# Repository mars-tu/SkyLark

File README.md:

# SkyLark
Repository of Drone named SkyLark by MARS capable of autonomous navigation for transfer of goods.

## Key Feature:-
* Autonomous robot with payload to carry for multiple purposes which is capable to move on RC control.
* Manipulate flight by gesture recognition.
* Runs on PX4 AutoPilot framework via ROS.

## Electro-mechanical design:

* Drone frame.

## Flight Controller Schematic:

## ROS Packages:
* [SkyLark package](#flying_skylark)

### flying_skylark
------------------
* This package contains all the files related to robot and its configuration 

### Setup and launching the simulation environment:-

* Clone the repo, build in your preferred system and add the following lines in your bashrc.
```
source ~/{name_of_workspace}/devel/setup.bash

source ~/{name_of_workspace}/src/PX4-Autopilot/Tools/setup_gazebo.bash ~/{name_of_workspace}/src/PX4-Autopilot/ ~/{name_of_workspace}/src/PX4-Autopilot/build/px4_sitl_default >> /dev/null

export ROS_PACKAGE_PATH=$ROS_PACKAGE_PATH:~/{name_of_workspace}/src/PX4-Autopilot

export ROS_PACKAGE_PATH=$ROS_PACKAGE_PATH:~/{name_of_workspace}/src/PX4-Autopilot/Tools/sitl_gazebo

```
* For making gazebo work with PX-4 autopilot 
```
cd ~/{name_of_workspace}/src/PX4-Autopilot/
make px4_sitl_default gazebo
```

* Command `roslaunch flying_skylark flying_square.launch` will launch the gazebo world along with the PX-4 autopilot.

### Simulation Video
Click on Image to play

## Prerequisites
* C++14
* python 2.x
* PX4 AutoPilot
* ROS Noetic
* Embedded C
* Raspberry pi 3B (setup given below)
* Eagle
* PTC Creo
#### Note: Hardware prerequisites mentioned in xyz section.

## Setup
* [Raspi + OS setup](#setting-up-cpu)

### Setting Up CPU
------------------
#### Installing Ubuntu and ROS on Raspberry pi
1) [Download](https://cdimage.ubuntu.com/releases/18.04/release/) the Ubuntu image for raspberry pi 3.
2) Flash the image with preferable software.
3) Follow the standard ARM installation instructions from [ROS Wiki](https://wiki.ros.org/melodic/Installation/Ubuntu) to install ROS Melodic.

#### Installing basic tools and setting them up
```
sudo apt-get update
sudo apt-get upgrade
sudo apt autoremove
```

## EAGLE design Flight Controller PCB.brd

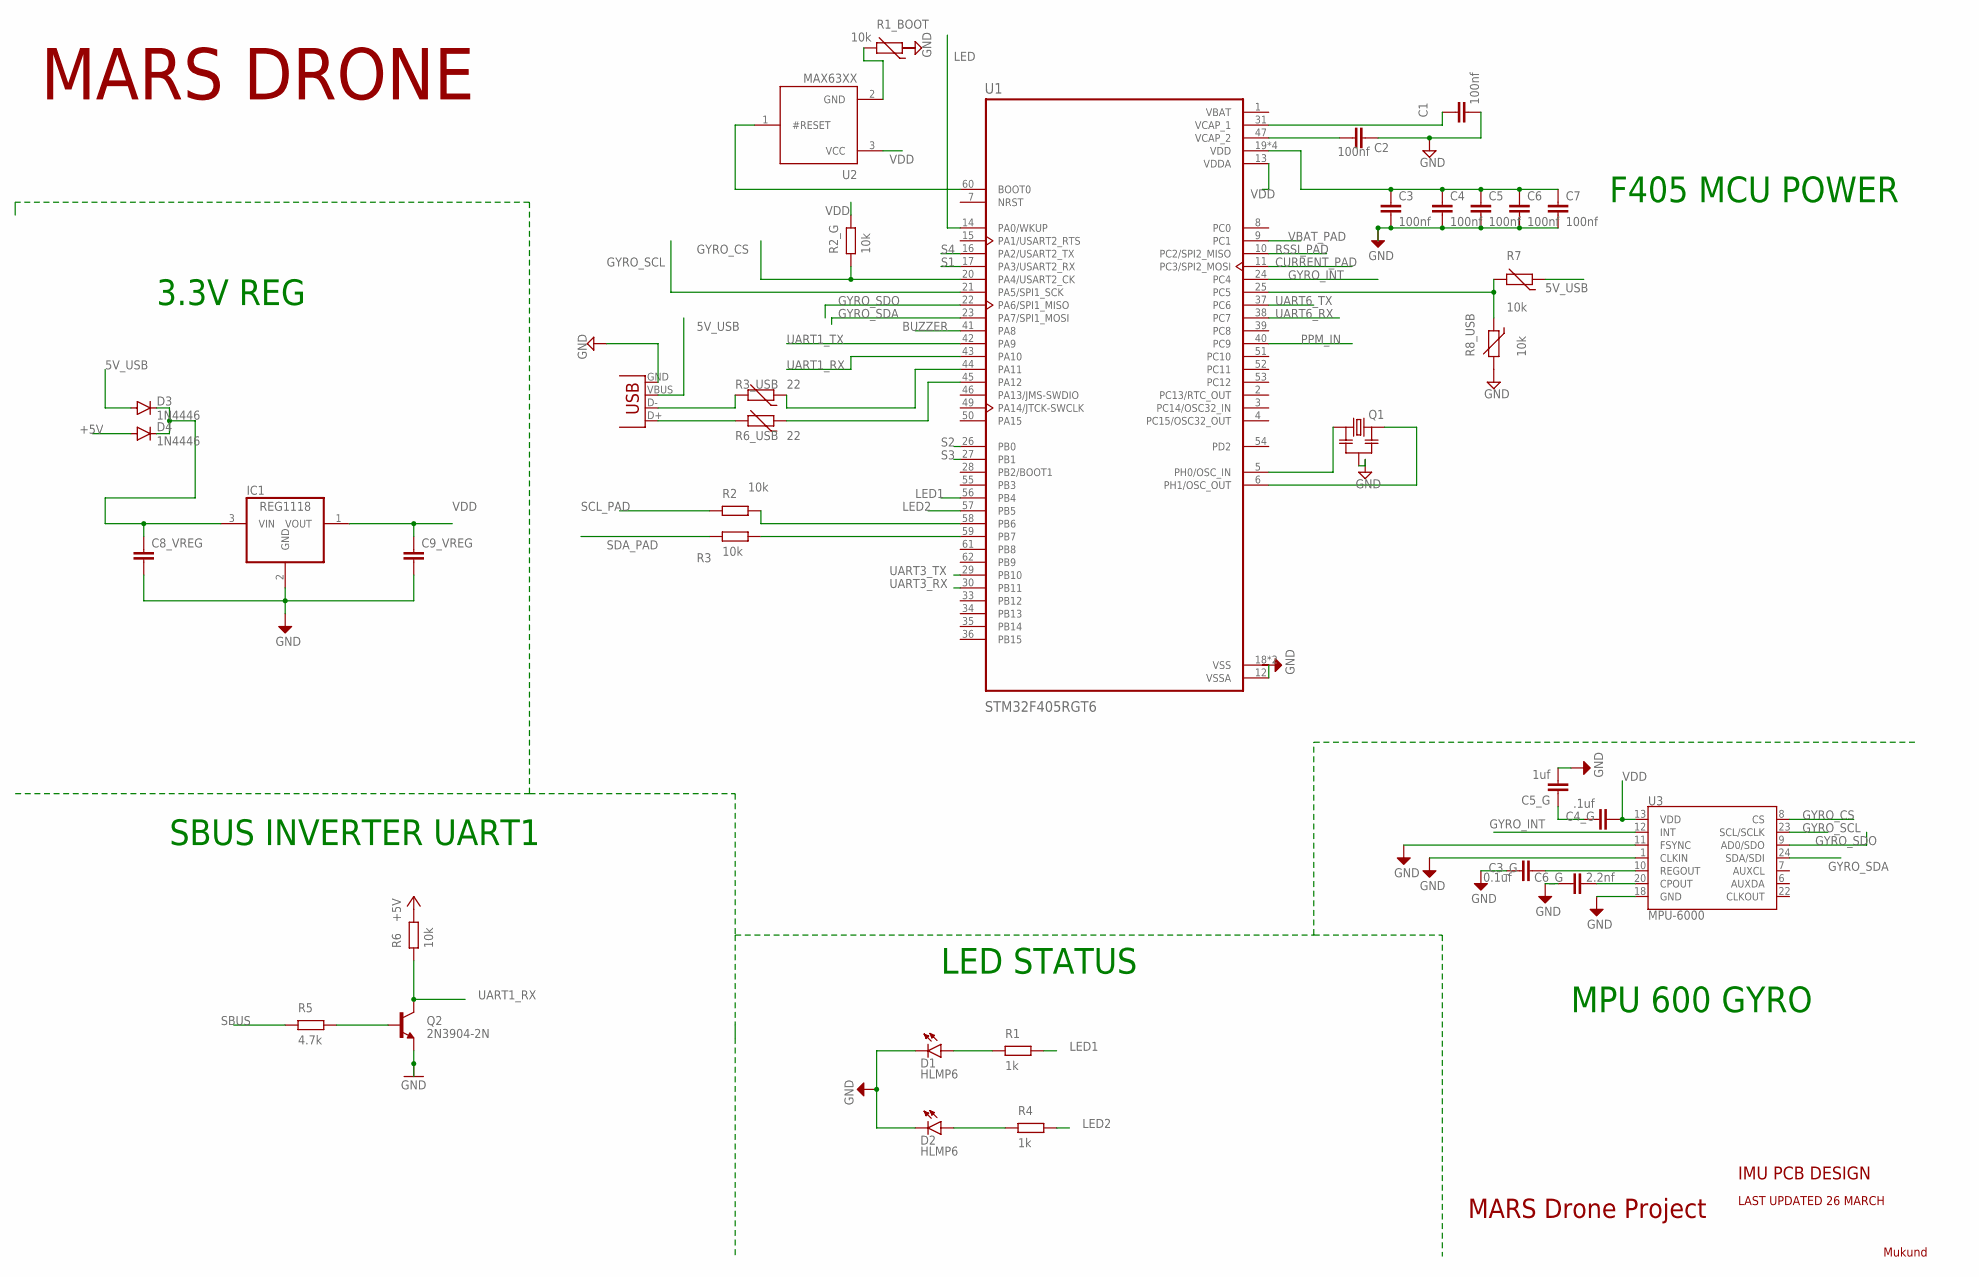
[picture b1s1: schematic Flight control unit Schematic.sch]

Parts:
C1, C2: 100nf; C2.5-3
C3, C4, C5, C6, C7: 100nf; C2.5-2
C3_G: 0.1uf; C2.5-3
C4_G: .1uf; C2.5-3
C5_G: 1uf; C2.5-3
C6_G: 2.2nf; C2.5-3
C8_VREG, C9_VREG: C2,5-3; C2.5-3
D1, D2: HLMP6
D3, D4: 1N4446; DO35-10
IC1: REG1118; SOT223
Q1: RESONATOR-MURATACST_CE; RESONATOR_MURATA2
Q2: 2N3904-2N; TO92
R1_BOOT, R7, R8_USB: 10k; RS-2,5
R3_USB, R6_USB: 22; RS-2,5
U1: STM32F405RGT6; QFP50P1200X1200X160-64N
U2: MAX63XX; SOT23
U3: MPU-6000; QFN-24-EP
X1: USB-A-S

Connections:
5V_USB: D3.A, R7.1, X1.VBUS
+5V: D4.A
BUZZER: U1.41 (PA8)
CURRENT_PAD: U1.11 (PC3/SPI2_MOSI)
GND: C1.2, C2.2, C3.2, C3_G.1, C4.2, C5.2, C5_G.2, C6.2, C6_G.1, C7.2, C8_VREG.2, C9_VREG.2, D1.K, D2.K, IC1.2 (GND), Q1.2, Q2.3 (E), R8_USB.2, U3.1 (CLKIN), U3.11 (FSYNC), U3.18 (GND), X1.GND
GYRO_CS: U1.20 (PA4/USART2_CK), U3.8 (CS)
GYRO_INT: U1.24 (PC4), U3.12 (INT)
GYRO_SCL: U1.21 (PA5/SPI1_SCK), U3.23 (SCL/SCLK)
GYRO_SDA: U1.23 (PA7/SPI1_MOSI), U3.24 (SDA/SDI)
GYRO_SDO: U1.22 (PA6/SPI1_MISO), U3.9 (AD0/SDO)
LED: U1.14 (PA0/WKUP)
LED1: U1.56 (PB4)
LED2: U1.57 (PB5)
unnamed: C6_G.2, U3.20 (CPOUT)
unnamed: U1.12 (VSSA), U1.18 (VSS), U1.63 (VSS)
unnamed: C4_G.1, C5_G.1
unnamed: C3.1, C4.1, C5.1, C6.1, C7.1, U1.19 (VDD), U1.32 (VDD), U1.48 (VDD), U1.64 (VDD)
unnamed: C3_G.2, U3.10 (REGOUT)
unnamed: R3_USB.1, U1.44 (PA11)
unnamed: R6_USB.1, U1.45 (PA12)
unnamed: C8_VREG.1, D3.C, D4.C, IC1.3 (VIN)
unnamed: R7.2, R8_USB.1, U1.25 (PC5)
unnamed: C1.1, U1.31 (VCAP_1)
unnamed: C2.1, U1.47 (VCAP_2)
unnamed: U1.60 (BOOT0), U2.1 (#RESET)
unnamed: R1_BOOT.2, U2.2 (GND)
unnamed: R6_USB.2, X1.D+
unnamed: R3_USB.2, X1.D-
unnamed: Q1.1, U1.5 (PH0/OSC_IN)
unnamed: Q1.3, U1.6 (PH1/OSC_OUT)
PPM_IN: U1.40 (PC9)
RSSI_PAD: U1.10 (PC2/SPI2_MISO)
S1: U1.17 (PA3/USART2_RX)
S2: U1.26 (PB0)
S3: U1.27 (PB1)
S4: U1.16 (PA2/USART2_TX)
UART1_RX: Q2.1 (C), U1.43 (PA10)
UART1_TX: U1.42 (PA9)
UART3_RX: U1.30 (PB11)
UART3_TX: U1.29 (PB10)
UART6_RX: U1.38 (PC7)
UART6_TX: U1.37 (PC6)
VBAT: U1.1 (VBAT)
VBAT_PAD: U1.9 (PC1)
VDD: C4_G.2, C9_VREG.1, IC1.1 (VOUT), U1.13 (VDDA), U2.3 (VCC), U3.13 (VDD)

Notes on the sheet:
F405 MCU POWER
MPU 600 GYRO
LED STATUS
SBUS INVERTER UART1
3.3V REG
LAST UPDATED 26 MARCH
MARS Drone Project
IMU PCB DESIGN
Mukund
MARS DRONE

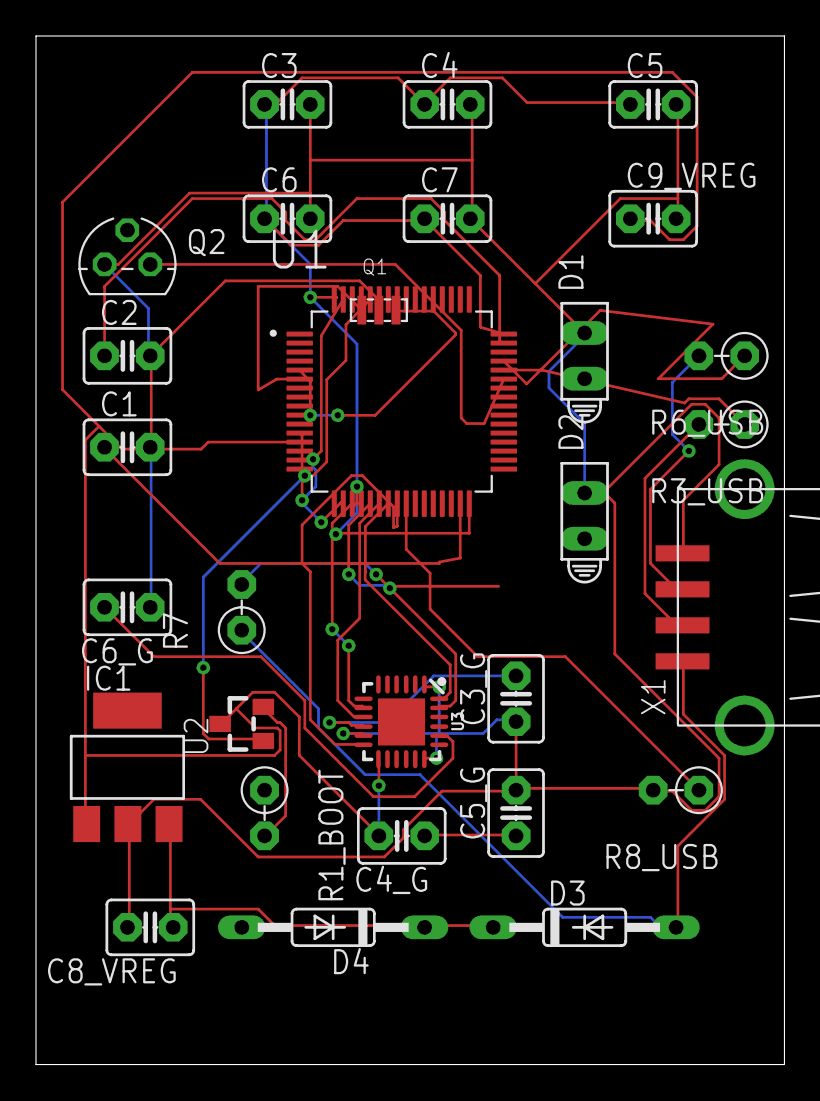
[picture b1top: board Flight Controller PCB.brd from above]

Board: 2 copper layers, 41.6 x 57.1 mm, 29 parts (0 on the bottom side), 26 nets.

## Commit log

2021-04-29 Schematic and PCB design of flight control that we will use
2021-04-29 Create new
2021-04-29 Rename Flight Controller PCB.brd to Boards/Flight Controller PCB.brd
2021-04-29 Rename Flight Controller Schematic.sch to Boards/Flight Controller Schematic.sch
2021-05-03 Contributors .txt file added
2021-12-21 Rename Boards/Flight Controller PCB.brd to Electronics/Flight Controller PCB.brd
2021-12-21 Rename Boards/Flight Controller Schematic.sch to Electronics/Flight Controller Schematic.sch
2021-12-21 Rename Electronics/Flight Controller PCB.brd to Electronics/Flight Controller/Flight Control Unit PCB.brd
2021-12-21 Rename Electronics/Flight Controller Schematic.sch to Electronics/Flight Controller/Flight control unit Schematic.sch
2021-12-21 Rename Readme.md to README.md
2021-12-21 Rename CAD/Analysis.wbpj to CAD/Analysis/Analysis.wbpj
2021-12-21 added skylark package
2021-12-22 Removed autopilot content

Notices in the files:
parts and their libraries:
m-pad-2.1: License : GNU General Public License version 2 (see bottom)
